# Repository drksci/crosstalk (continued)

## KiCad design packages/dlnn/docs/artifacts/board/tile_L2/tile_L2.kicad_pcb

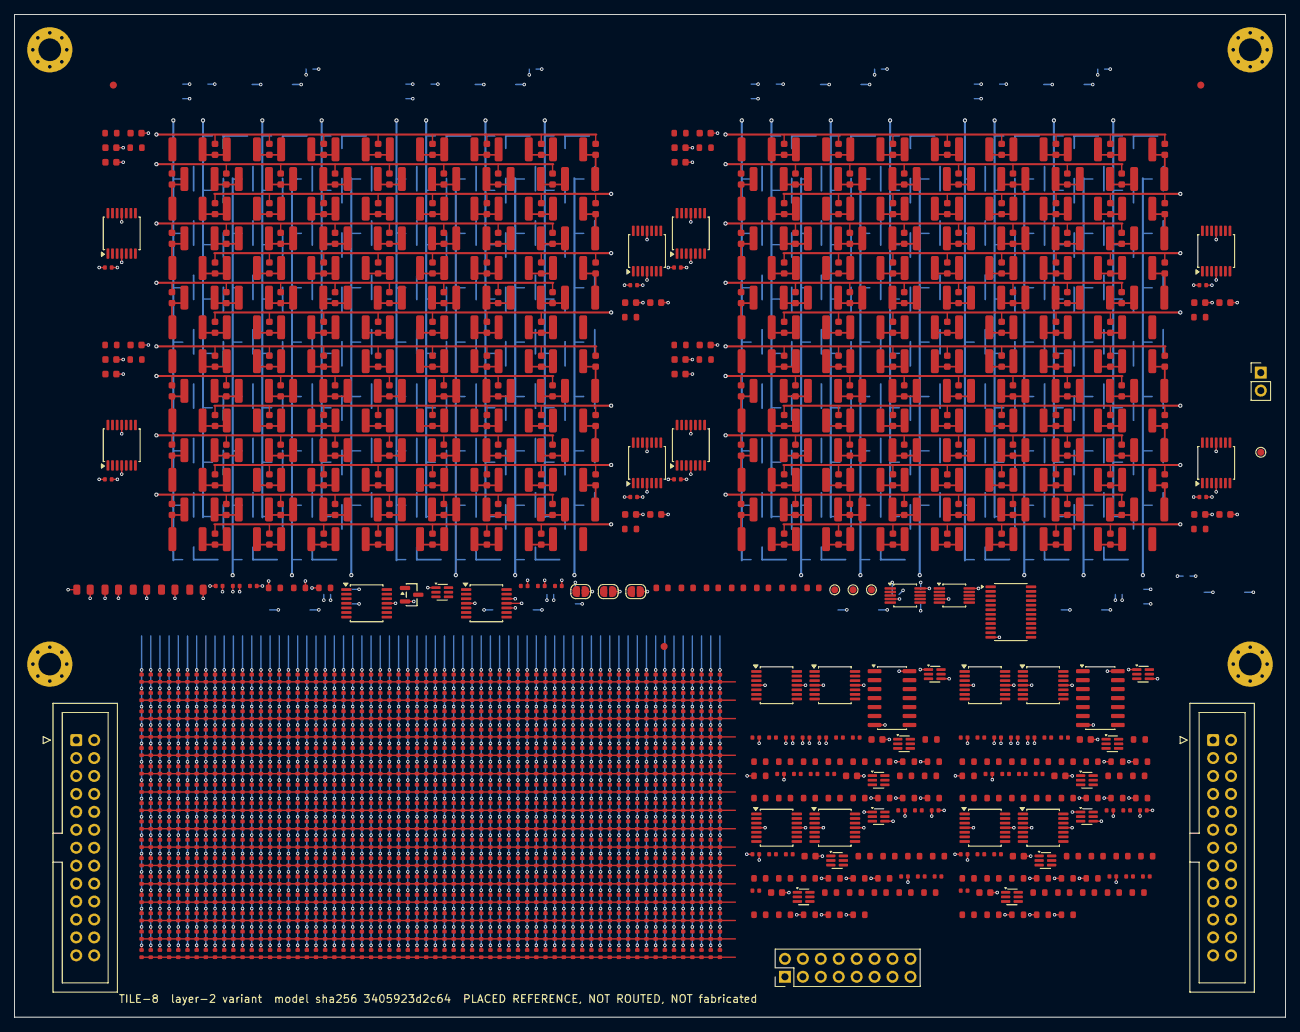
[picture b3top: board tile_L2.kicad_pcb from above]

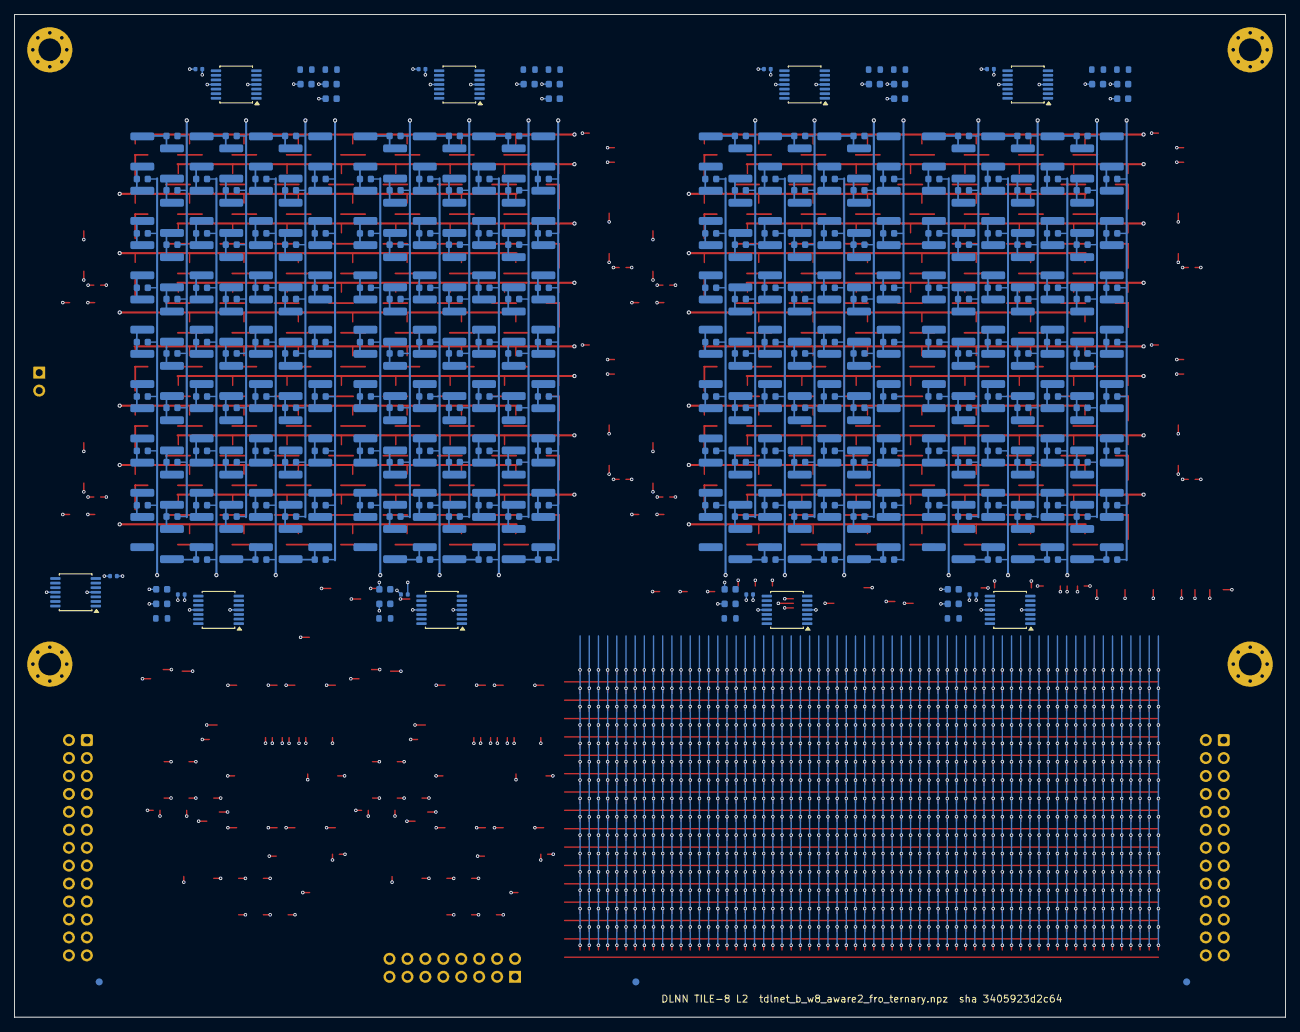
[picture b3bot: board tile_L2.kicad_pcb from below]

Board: 4 copper layers, 180.0 x 142.0 mm, 2211 parts (497 on the bottom side), 668 nets.

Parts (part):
C0_0_1, C0_0_2, C0_56_1, C0_56_2, C1_0_1, C1_0_2, C1_56_1, C1_56_2, C2_0_1, C2_0_2, C2_56_1, C2_56_2, C3_0_1, C3_0_2, C3_56_1, C3_56_2, C4_0_1, C4_0_2, C4_56_1, C4_56_2, C5_0_1, C5_0_2, C5_56_1, C5_56_2, C6_0_1, C6_0_2, C6_56_1, C6_56_2, C7_0_1, C7_0_2, C7_56_1, C7_56_2: 30p; C_0603_1608Metric
C0_1, C0_2, C0_3, C0_4, C0_5, C0_6, C0_7, C0_8, C0_9, C0_10, C0_11, C0_12, C0_13, C0_14, C0_15, C0_16, C0_17, C0_18, C0_19, C0_20, C0_21, C0_22, C0_23, C0_24, C0_25, C0_26, C0_27, C0_28, C0_29, C0_30, C0_31, C0_32, C0_33, C0_34, C0_35, C0_36, C0_37, C0_38, C0_39, C0_40, C0_41, C0_42, C0_43, C0_44, C0_45, C0_46, C0_47, C0_48, C0_49, C0_50, C0_51, C0_52, C0_53, C0_54, C0_55, C1_1, C1_2, C1_3, C1_4, C1_5, C1_6, C1_7, C1_8, C1_9, C1_10, C1_11, C1_12, C1_13, C1_14, C1_15, C1_16, C1_17, C1_18, C1_19, C1_20, C1_21, C1_22, C1_23, C1_24, C1_25, C1_26, C1_27, C1_28, C1_29, C1_30, C1_31, C1_32, C1_33, C1_34, C1_35, C1_36, C1_37, C1_38, C1_39, C1_40, C1_41, C1_42, C1_43, C1_44, C1_45, C1_46, C1_47, C1_48, C1_49, C1_50, C1_51, C1_52, C1_53, C1_54, C1_55, C2_1, C2_2, C2_3, C2_4, C2_5, C2_6, C2_7, C2_8, C2_9, C2_10, C2_11, C2_12, C2_13, C2_14, C2_15, C2_16, C2_17, C2_18, C2_19, C2_20, C2_21, C2_22, C2_23, C2_24, C2_25, C2_26, C2_27, C2_28, C2_29, C2_30, C2_31, C2_32, C2_33, C2_34, C2_35, C2_36, C2_37, C2_38, C2_39, C2_40, C2_41, C2_42, C2_43, C2_44, C2_45, C2_46, C2_47, C2_48, C2_49, C2_50, C2_51, C2_52, C2_53, C2_54, C2_55, C3_1, C3_2, C3_3, C3_4, C3_5, C3_6, C3_7, C3_8, C3_9, C3_10, C3_11, C3_12, C3_13, C3_14, C3_15, C3_16, C3_17, C3_18, C3_19, C3_20, C3_21, C3_22, C3_23, C3_24, C3_25, C3_26, C3_27, C3_28, C3_29, C3_30, C3_31, C3_32, C3_33, C3_34, C3_35, C3_36, C3_37, C3_38, C3_39, C3_40, C3_41, C3_42, C3_43, C3_44, C3_45, C3_46, C3_47, C3_48, C3_49, C3_50, C3_51, C3_52, C3_53, C3_54, C3_55, C4_1, C4_2, C4_3, C4_4, C4_5, C4_6, C4_7, C4_8, C4_9, C4_10, C4_11, C4_12, C4_13, C4_14, C4_15, C4_16, C4_17, C4_18, C4_19, C4_20, C4_21, C4_22, C4_23, C4_24, C4_25, C4_26, C4_27, C4_28, C4_29, C4_30, C4_31, C4_32, C4_33, C4_34, C4_35, C4_36, C4_37, C4_38, C4_39, C4_40, C4_41, C4_42, C4_43, C4_44, C4_45, C4_46, C4_47, C4_48, C4_49, C4_50, C4_51, C4_52, C4_53, C4_54, C4_55, C5_1, C5_2, C5_3, C5_4, C5_5, C5_6, C5_7, C5_8, C5_9, C5_10, C5_11, C5_12, C5_13, C5_14, C5_15, C5_16, C5_17, C5_18, C5_19, C5_20, C5_21, C5_22, C5_23, C5_24, C5_25, C5_26, C5_27, C5_28, C5_29, C5_30, C5_31, C5_32, C5_33, C5_34, C5_35, C5_36, C5_37, C5_38, C5_39, C5_40, C5_41, C5_42, C5_43, C5_44, C5_45, C5_46, C5_47, C5_48, C5_49, C5_50, C5_51, C5_52, C5_53, C5_54, C5_55, C6_1, C6_2, C6_3, C6_4, C6_5, C6_6, C6_7, C6_8, C6_9, C6_10, C6_11, C6_12, C6_13, C6_14, C6_15, C6_16, C6_17, C6_18, C6_19, C6_20, C6_21, C6_22, C6_23, C6_24, C6_25, C6_26, C6_27, C6_28, C6_29, C6_30, C6_31, C6_32, C6_33, C6_34, C6_35, C6_36, C6_37, C6_38, C6_39, C6_40, C6_41, C6_42, C6_43, C6_44, C6_45, C6_46, C6_47, C6_48, C6_49, C6_50, C6_51, C6_52, C6_53, C6_54, C6_55, C7_1, C7_2, C7_3, C7_4, C7_5, C7_6, C7_7, C7_8, C7_9, C7_10, C7_11, C7_12, C7_13, C7_14, C7_15, C7_16, C7_17, C7_18, C7_19, C7_20, C7_21, C7_22, C7_23, C7_24, C7_25, C7_26, C7_27, C7_28, C7_29, C7_30, C7_31, C7_32, C7_33, C7_34, C7_35, C7_36, C7_37, C7_38, C7_39, C7_40, C7_41, C7_42, C7_43, C7_44, C7_45, C7_46, C7_47, C7_48, C7_49, C7_50, C7_51, C7_52, C7_53, C7_54, C7_55: 120p; C_0603_1608Metric
CB1, CB2, CB3, CB4, CB5: 10u; C_0805_2012Metric
CBF0, CBF1, CBF2, CBF3, CBF4, CBF5, CBF6, CBF7: 100n; C_0402_1005Metric
CDA0, CDA1, CDA2, CDA3, CDA4, CDA5, CDA6, CDA7: 8.2p; C_0402_1005Metric
CDCS0, CDCS1, CDCS2, CDCS3: 100n; C_0402_1005Metric
CDDA0, CDDA1, CDDA2, CDDA3: 100n; C_0402_1005Metric
CDDAC0, CDDAC1: 100n; C_0402_1005Metric
CDIB0, CDIB1: 100n; C_0402_1005Metric
CDMUX1: 100n; C_0402_1005Metric
CDSH0, CDSH1: 100n; C_0402_1005Metric
CDTA0, CDTA1, CDTA2, CDTA3, CDTA4, CDTA5, CDTA6, CDTA7: 100n; C_0402_1005Metric
CDTB0, CDTB1, CDTB2, CDTB3, CDTB4, CDTB5, CDTB6, CDTB7: 100n; C_0402_1005Metric
CDVR1: 100n; C_0402_1005Metric
CFN0, CFN1, CFN2, CFN3, CFN4, CFN5, CFN6, CFN7: 15p; C_0402_1005Metric
CFP0, CFP1, CFP2, CFP3, CFP4, CFP5, CFP6, CFP7: 15p; C_0402_1005Metric
CH0, CH1, CH2, CH3, CH4, CH5, CH6, CH7: 560p; C_0603_1608Metric
CP0, CP1, CP2, CP3, CP4, CP5, CP6, CP7: 330p; C_0603_1608Metric
CREF1: 100n; C_0402_1005Metric
FID1, FID2, FID3, FID4, FID5, FID6: Fiducial_1mm_Mask2mm
H1, H2, H3, H4: MountingHole_3.2mm_M3_Pad_Via
JIN1: 2x13 IDC; IDC-Header_2x13_P2.54mm_Vertical
JMON1: MON; PinHeader_1x02_P2.54mm_Vertical
JOUT1: 2x13 IDC; IDC-Header_2x13_P2.54mm_Vertical
JPID0, JPID1, JPID2: ID; SolderJumper-2_P1.3mm_Open_RoundedPad1.0x1.5mm
JPS1: J_PS 2x8; PinHeader_2x08_P2.54mm_Vertical
L0_1, L0_2, L0_3, L0_4, L0_5, L0_6, L0_7, L0_8, L0_9, L0_10, L0_11, L0_12, L0_13, L0_14, L0_15, L0_16, L0_17, L0_18, L0_19, L0_20, L0_21, L0_22, L0_23, L0_24, L0_25, L0_26, L0_27, L0_28, L0_29, L0_30, L0_31, L0_32, L0_33, L0_34, L0_35, L0_36, L0_37, L0_38, L0_39, L0_40, L0_41, L0_42, L0_43, L0_44, L0_45, L0_46, L0_47, L0_48, L0_49, L0_50, L0_51, L0_52, L0_53, L0_54, L0_55, L0_56, L1_1, L1_2, L1_3, L1_4, L1_5, L1_6, L1_7, L1_8, L1_9, L1_10, L1_11, L1_12, L1_13, L1_14, L1_15, L1_16, L1_17, L1_18, L1_19, L1_20, L1_21, L1_22, L1_23, L1_24, L1_25, L1_26, L1_27, L1_28, L1_29, L1_30, L1_31, L1_32, L1_33, L1_34, L1_35, L1_36, L1_37, L1_38, L1_39, L1_40, L1_41, L1_42, L1_43, L1_44, L1_45, L1_46, L1_47, L1_48, L1_49, L1_50, L1_51, L1_52, L1_53, L1_54, L1_55, L1_56, L2_1, L2_2, L2_3, L2_4, L2_5, L2_6, L2_7, L2_8, L2_9, L2_10, L2_11, L2_12, L2_13, L2_14, L2_15, L2_16, L2_17, L2_18, L2_19, L2_20, L2_21, L2_22, L2_23, L2_24, L2_25, L2_26, L2_27, L2_28, L2_29, L2_30, L2_31, L2_32, L2_33, L2_34, L2_35, L2_36, L2_37, L2_38, L2_39, L2_40, L2_41, L2_42, L2_43, L2_44, L2_45, L2_46, L2_47, L2_48, L2_49, L2_50, L2_51, L2_52, L2_53, L2_54, L2_55, L2_56, L3_1, L3_2, L3_3, L3_4, L3_5, L3_6, L3_7, L3_8, L3_9, L3_10, L3_11, L3_12, L3_13, L3_14, L3_15, L3_16, L3_17, L3_18, L3_19, L3_20, L3_21, L3_22, L3_23, L3_24, L3_25, L3_26, L3_27, L3_28, L3_29, L3_30, L3_31, L3_32, L3_33, L3_34, L3_35, L3_36, L3_37, L3_38, L3_39, L3_40, L3_41, L3_42, L3_43, L3_44, L3_45, L3_46, L3_47, L3_48, L3_49, L3_50, L3_51, L3_52, L3_53, L3_54, L3_55, L3_56, L4_1, L4_2, L4_3, L4_4, L4_5, L4_6, L4_7, L4_8, L4_9, L4_10, L4_11, L4_12, L4_13, L4_14, L4_15, L4_16, L4_17, L4_18, L4_19, L4_20, L4_21, L4_22, L4_23, L4_24, L4_25, L4_26, L4_27, L4_28, L4_29, L4_30, L4_31, L4_32, L4_33, L4_34, L4_35, L4_36, L4_37, L4_38, L4_39, L4_40, L4_41, L4_42, L4_43, L4_44, L4_45, L4_46, L4_47, L4_48, L4_49, L4_50, L4_51, L4_52, L4_53, L4_54, L4_55, L4_56, L5_1, L5_2, L5_3, L5_4, L5_5, L5_6, L5_7, L5_8, L5_9, L5_10, L5_11, L5_12, L5_13, L5_14, L5_15, L5_16, L5_17, L5_18, L5_19, L5_20, L5_21, L5_22, L5_23, L5_24, L5_25, L5_26, L5_27, L5_28, L5_29, L5_30, L5_31, L5_32, L5_33, L5_34, L5_35, L5_36, L5_37, L5_38, L5_39, L5_40, L5_41, L5_42, L5_43, L5_44, L5_45, L5_46, L5_47, L5_48, L5_49, L5_50, L5_51, L5_52, L5_53, L5_54, L5_55, L5_56, L6_1, L6_2, L6_3, L6_4, L6_5, L6_6, L6_7, L6_8, L6_9, L6_10, L6_11, L6_12, L6_13, L6_14, L6_15, L6_16, L6_17, L6_18, L6_19, L6_20, L6_21, L6_22, L6_23, L6_24, L6_25, L6_26, L6_27, L6_28, L6_29, L6_30, L6_31, L6_32, L6_33, L6_34, L6_35, L6_36, L6_37, L6_38, L6_39, L6_40, L6_41, L6_42, L6_43, L6_44, L6_45, L6_46, L6_47, L6_48, L6_49, L6_50, L6_51, L6_52, L6_53, L6_54, L6_55, L6_56, L7_1, L7_2, L7_3, L7_4, L7_5, L7_6, L7_7, L7_8, L7_9, L7_10, L7_11, L7_12, L7_13, L7_14, L7_15, L7_16, L7_17, L7_18, L7_19, L7_20, L7_21, L7_22, L7_23, L7_24, L7_25, L7_26, L7_27, L7_28, L7_29, L7_30, L7_31, L7_32, L7_33, L7_34, L7_35, L7_36, L7_37, L7_38, L7_39, L7_40, L7_41, L7_42, L7_43, L7_44, L7_45, L7_46, L7_47, L7_48, L7_49, L7_50, L7_51, L7_52, L7_53, L7_54, L7_55, L7_56: 120u; L_1812_4532Metric
QD0, QD1, QD2, QD3, QD4, QD5, QD6, QD7: BCM847BS; SOT-363_SC-70-6
RB0, RB1, RB2, RB3, RB4, RB5, RB6, RB7: 9.09k; R_0603_1608Metric
RDA1_0, RDA1_1, RDA1_2, RDA1_3, RDA1_4, RDA1_5, RDA1_6, RDA1_7, RDA3_0, RDA3_1, RDA3_2, RDA3_3, RDA3_4, RDA3_5, RDA3_6, RDA3_7: 20k; R_0603_1608Metric
RDA2_0, RDA2_1, RDA2_2, RDA2_3, RDA2_4, RDA2_5, RDA2_6, RDA2_7, RDA4_0, RDA4_1, RDA4_2, RDA4_3, RDA4_4, RDA4_5, RDA4_6, RDA4_7: 10.5k; R_0603_1608Metric
RFN0, RFN1, RFN2, RFN3, RFN4, RFN5, RFN6, RFN7: 1.05k; R_0603_1608Metric
RFP0, RFP1, RFP2, RFP3, RFP4, RFP5, RFP6, RFP7: 1.05k; R_0603_1608Metric
RID0, RID1, RID2: 10k; R_0603_1608Metric
RLD1_0, RLD1_1, RLD1_2, RLD1_3, RLD1_4, RLD1_5, RLD1_6, RLD1_7, RLD2_0, RLD2_1, RLD2_2, RLD2_3, RLD2_4, RLD2_5, RLD2_6, RLD2_7: 1k; R_0603_1608Metric
RMIR1: 4.32k; R_0603_1608Metric
RO0, RO1, RO2, RO3, RO4, RO5, RO6, RO7: 15.4k; R_0603_1608Metric
RP0, RP1, RP2, RP3, RP4, RP5, RP6, RP7: 1k; R_0603_1608Metric
RPD1: 10k; R_0603_1608Metric
RPU1, RPU2, RPU3, RPU4: 10k; R_0603_1608Metric
RREF1: 2.49k; R_0603_1608Metric
RS0, RS1, RS2, RS3, RS4, RS5, RS6, RS7: 1k; R_0603_1608Metric
RT0, RT1, RT2, RT3, RT4, RT5, RT6, RT7: 1k; R_0603_1608Metric
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
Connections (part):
+3V3: CB3.1, CDDAC0.1, CDDAC1.1, CDMUX1.1, JIN1.21, JOUT1.21, RID0.1, RID1.1, RID2.1, RPU1.1, RPU2.1, RPU3.1, RPU4.1, UDAC0.1, UDAC1.1, UMUX1.3, UMUX1.24
+5VA: CB1.1, CB2.1, CDCS0.1, CDCS1.1, CDCS2.1, CDCS3.1, CDDA0.1, CDDA1.1, CDDA2.1, CDDA3.1, CDIB0.1, CDIB1.1, CDSH0.1, CDSH1.1, CDTA0.1, CDTA1.1, CDTA2.1, CDTA3.1, CDTA4.1, CDTA5.1, CDTA6.1, CDTA7.1, CDTB0.1, CDTB1.1, CDTB2.1, CDTB3.1, CDTB4.1, CDTB5.1, CDTB6.1, CDTB7.1, CDVR1.1, JIN1.17, JIN1.19, JOUT1.17, JOUT1.19, RLD1_0.1, RLD1_1.1, RLD1_2.1, RLD1_3.1, RLD1_4.1, RLD1_5.1, RLD1_6.1, RLD1_7.1, RLD2_0.1, RLD2_1.1, RLD2_2.1, RLD2_3.1, RLD2_4.1, RLD2_5.1, RLD2_6.1, RLD2_7.1, RMIR1.1, RO0.1, RO1.1, RO2.1, RO3.1, RO4.1, RO5.1, RO6.1, RO7.1, RREF1.1, UCS0.4, UCS1.4, UCS2.4, UCS3.4, UDA0.4, UDA1.4, UDA2.4, UDA3.4, UIB0.4, UIB1.4, USH0.14, USH1.14, UTA0.4, UTA1.4, UTA2.4, UTA3.4, UTA4.4, UTA5.4, UTA6.4, UTA7.4, UTB0.4, UTB1.4, UTB2.4, UTB3.4, UTB4.4, UTB5.4, UTB6.4, UTB7.4, UVR1.4
/ch0/DAIN: CDA0.1, RDA3_0.2, RDA4_0.1, UDA0.2
/ch0/DAIP: RDA1_0.2, RDA2_0.1, UDA0.3
/ch0/DAO: CDA0.2, RDA4_0.2, UDA0.1, USH0.1
/ch0/DC1: QD0.6, RDA1_0.1, RLD1_0.2
/ch0/DC2: QD0.3, RDA3_0.1, RLD2_0.2
/ch0/HOLD: CH0.1, UDA0.5, USH0.2
/ch0/ON: CFN0.2, QD0.2, RFN0.2, UCS0.7
/ch0/OP: CFP0.2, QD0.5, RFP0.2, UCS0.1
/ch0/TAIL: QD0.1, QD0.4, UT0.6
/ch1/DAIN: CDA1.1, RDA3_1.2, RDA4_1.1, UDA0.9
/ch1/DAIP: RDA1_1.2, RDA2_1.1, UDA0.10
/ch1/DAO: CDA1.2, RDA4_1.2, UDA0.8, USH0.4
/ch1/DC1: QD1.6, RDA1_1.1, RLD1_1.2
/ch1/DC2: QD1.3, RDA3_1.1, RLD2_1.2
/ch1/HOLD: CH1.1, UDA0.12, USH0.3
/ch1/ON: CFN1.2, QD1.2, RFN1.2, UCS0.14
/ch1/OP: CFP1.2, QD1.5, RFP1.2, UCS0.8
/ch1/TAIL: QD1.1, QD1.4, UT0.3
/ch2/DAIN: CDA2.1, RDA3_2.2, RDA4_2.1, UDA1.2
/ch2/DAIP: RDA1_2.2, RDA2_2.1, UDA1.3
/ch2/DAO: CDA2.2, RDA4_2.2, UDA1.1, USH0.8
/ch2/DC1: QD2.6, RDA1_2.1, RLD1_2.2
/ch2/DC2: QD2.3, RDA3_2.1, RLD2_2.2
/ch2/HOLD: CH2.1, UDA1.5, USH0.9
/ch2/ON: CFN2.2, QD2.2, RFN2.2, UCS1.7
/ch2/OP: CFP2.2, QD2.5, RFP2.2, UCS1.1
/ch2/TAIL: QD2.1, QD2.4, UT1.6
/ch3/DAIN: CDA3.1, RDA3_3.2, RDA4_3.1, UDA1.9
/ch3/DAIP: RDA1_3.2, RDA2_3.1, UDA1.10
/ch3/DAO: CDA3.2, RDA4_3.2, UDA1.8, USH0.11
/ch3/DC1: QD3.6, RDA1_3.1, RLD1_3.2
/ch3/DC2: QD3.3, RDA3_3.1, RLD2_3.2
/ch3/HOLD: CH3.1, UDA1.12, USH0.10
/ch3/ON: CFN3.2, QD3.2, RFN3.2, UCS1.14
/ch3/OP: CFP3.2, QD3.5, RFP3.2, UCS1.8
/ch3/TAIL: QD3.1, QD3.4, UT1.3
/ch4/DAIN: CDA4.1, RDA3_4.2, RDA4_4.1, UDA2.2
/ch4/DAIP: RDA1_4.2, RDA2_4.1, UDA2.3
/ch4/DAO: CDA4.2, RDA4_4.2, UDA2.1, USH1.1
/ch4/DC1: QD4.6, RDA1_4.1, RLD1_4.2
/ch4/DC2: QD4.3, RDA3_4.1, RLD2_4.2
/ch4/HOLD: CH4.1, UDA2.5, USH1.2
/ch4/ON: CFN4.2, QD4.2, RFN4.2, UCS2.7
/ch4/OP: CFP4.2, QD4.5, RFP4.2, UCS2.1
/ch4/TAIL: QD4.1, QD4.4, UT2.6
/ch5/DAIN: CDA5.1, RDA3_5.2, RDA4_5.1, UDA2.9
/ch5/DAIP: RDA1_5.2, RDA2_5.1, UDA2.10
/ch5/DAO: CDA5.2, RDA4_5.2, UDA2.8, USH1.4
/ch5/DC1: QD5.6, RDA1_5.1, RLD1_5.2
/ch5/DC2: QD5.3, RDA3_5.1, RLD2_5.2
/ch5/HOLD: CH5.1, UDA2.12, USH1.3
/ch5/ON: CFN5.2, QD5.2, RFN5.2, UCS2.14
/ch5/OP: CFP5.2, QD5.5, RFP5.2, UCS2.8
/ch5/TAIL: QD5.1, QD5.4, UT2.3
/ch6/DAIN: CDA6.1, RDA3_6.2, RDA4_6.1, UDA3.2
/ch6/DAIP: RDA1_6.2, RDA2_6.1, UDA3.3
/ch6/DAO: CDA6.2, RDA4_6.2, UDA3.1, USH1.8
/ch6/DC1: QD6.6, RDA1_6.1, RLD1_6.2
/ch6/DC2: QD6.3, RDA3_6.1, RLD2_6.2
/ch6/HOLD: CH6.1, UDA3.5, USH1.9
/ch6/ON: CFN6.2, QD6.2, RFN6.2, UCS3.7
/ch6/OP: CFP6.2, QD6.5, RFP6.2, UCS3.1
/ch6/TAIL: QD6.1, QD6.4, UT3.6
/ch7/DAIN: CDA7.1, RDA3_7.2, RDA4_7.1, UDA3.9
/ch7/DAIP: RDA1_7.2, RDA2_7.1, UDA3.10
/ch7/DAO: CDA7.2, RDA4_7.2, UDA3.8, USH1.11
/ch7/DC1: QD7.6, RDA1_7.1, RLD1_7.2
/ch7/DC2: QD7.3, RDA3_7.1, RLD2_7.2
/ch7/HOLD: CH7.1, UDA3.12, USH1.10
/ch7/ON: CFN7.2, QD7.2, RFN7.2, UCS3.14
/ch7/OP: CFP7.2, QD7.5, RFP7.2, UCS3.8
/ch7/TAIL: QD7.1, QD7.4, UT3.3
/connectors/SCL0: RPU2.2, UDAC0.2, UMUX1.5
/connectors/SCL1: RPU4.2, UDAC1.2, UMUX1.7
/connectors/SDA0: RPU1.2, UDAC0.3, UMUX1.4
/connectors/SDA1: RPU3.2, UDAC1.3, UMUX1.6
/connectors/TID0: JPID0.1, RID0.2, TPID0.1, UMUX1.1
/connectors/TID1: JPID1.1, RID1.2, TPID1.1, UMUX1.2
/connectors/TID2: JPID2.1, RID2.2, TPID2.1, UMUX1.21
/line0/IB: RS0.1, UIB0.1, UIB0.2
/line0/N0: C0_0_1.1, C0_0_2.1, L0_1.1, RS0.2, UTA0.3
/line0/N8: C0_8.1, L0_8.2, L0_9.1, UTB0.3
/line0/N16: C0_16.1, L0_16.2, L0_17.1, UTA0.5
/line0/N24: C0_24.1, L0_24.2, L0_25.1, UTB0.5
/line0/N28: C0_28.1, L0_28.2, L0_29.1
/line0/N32: C0_32.1, L0_32.2, L0_33.1, UTA0.10
/line0/N40: C0_40.1, L0_40.2, L0_41.1, UTB0.10
/line0/N48: C0_48.1, L0_48.2, L0_49.1, UTA0.12
/line0/N56: C0_56_1.1, C0_56_2.1, L0_56.2, RT0.1, UTB0.12
/line0/RC: CP0.1, RP0.2, UIB0.3
/line1/IB: RS1.1, UIB0.6, UIB0.7
/line1/N0: C1_0_1.1, C1_0_2.1, L1_1.1, RS1.2, UTA1.3
/line1/N8: C1_8.1, L1_8.2, L1_9.1, UTB1.3
/line1/N16: C1_16.1, L1_16.2, L1_17.1, UTA1.5
/line1/N24: C1_24.1, L1_24.2, L1_25.1, UTB1.5
/line1/N28: C1_28.1, L1_28.2, L1_29.1
/line1/N32: C1_32.1, L1_32.2, L1_33.1, UTA1.10
/line1/N40: C1_40.1, L1_40.2, L1_41.1, UTB1.10
/line1/N48: C1_48.1, L1_48.2, L1_49.1, UTA1.12
/line1/N56: C1_56_1.1, C1_56_2.1, L1_56.2, RT1.1, UTB1.12
/line1/RC: CP1.1, RP1.2, UIB0.5
/line2/IB: RS2.1, UIB0.8, UIB0.9
/line2/N0: C2_0_1.1, C2_0_2.1, L2_1.1, RS2.2, UTA2.3
/line2/N8: C2_8.1, L2_8.2, L2_9.1, UTB2.3
/line2/N16: C2_16.1, L2_16.2, L2_17.1, UTA2.5
/line2/N24: C2_24.1, L2_24.2, L2_25.1, UTB2.5
/line2/N28: C2_28.1, L2_28.2, L2_29.1
/line2/N32: C2_32.1, L2_32.2, L2_33.1, UTA2.10
/line2/N40: C2_40.1, L2_40.2, L2_41.1, UTB2.10
/line2/N48: C2_48.1, L2_48.2, L2_49.1, UTA2.12
/line2/N56: C2_56_1.1, C2_56_2.1, L2_56.2, RT2.1, UTB2.12
/line2/RC: CP2.1, RP2.2, UIB0.10
/line3/IB: RS3.1, UIB0.13, UIB0.14
/line3/N0: C3_0_1.1, C3_0_2.1, L3_1.1, RS3.2, UTA3.3
/line3/N8: C3_8.1, L3_8.2, L3_9.1, UTB3.3
/line3/N16: C3_16.1, L3_16.2, L3_17.1, UTA3.5
/line3/N24: C3_24.1, L3_24.2, L3_25.1, UTB3.5
/line3/N28: C3_28.1, L3_28.2, L3_29.1
/line3/N32: C3_32.1, L3_32.2, L3_33.1, UTA3.10
/line3/N40: C3_40.1, L3_40.2, L3_41.1, UTB3.10
/line3/N48: C3_48.1, L3_48.2, L3_49.1, UTA3.12
/line3/N56: C3_56_1.1, C3_56_2.1, L3_56.2, RT3.1, UTB3.12
/line3/RC: CP3.1, RP3.2, UIB0.12
/line4/IB: RS4.1, UIB1.1, UIB1.2
/line4/N0: C4_0_1.1, C4_0_2.1, L4_1.1, RS4.2, UTA4.3
/line4/N8: C4_8.1, L4_8.2, L4_9.1, UTB4.3
/line4/N16: C4_16.1, L4_16.2, L4_17.1, UTA4.5
/line4/N24: C4_24.1, L4_24.2, L4_25.1, UTB4.5
/line4/N28: C4_28.1, L4_28.2, L4_29.1
/line4/N32: C4_32.1, L4_32.2, L4_33.1, UTA4.10
/line4/N40: C4_40.1, L4_40.2, L4_41.1, UTB4.10
/line4/N48: C4_48.1, L4_48.2, L4_49.1, UTA4.12
/line4/N56: C4_56_1.1, C4_56_2.1, L4_56.2, RT4.1, UTB4.12
/line4/RC: CP4.1, RP4.2, UIB1.3
/line5/IB: RS5.1, UIB1.6, UIB1.7
/line5/N0: C5_0_1.1, C5_0_2.1, L5_1.1, RS5.2, UTA5.3
/line5/N8: C5_8.1, L5_8.2, L5_9.1, UTB5.3
/line5/N16: C5_16.1, L5_16.2, L5_17.1, UTA5.5
/line5/N24: C5_24.1, L5_24.2, L5_25.1, UTB5.5
/line5/N28: C5_28.1, L5_28.2, L5_29.1
/line5/N32: C5_32.1, L5_32.2, L5_33.1, UTA5.10
/line5/N40: C5_40.1, L5_40.2, L5_41.1, UTB5.10
/line5/N48: C5_48.1, L5_48.2, L5_49.1, UTA5.12
/line5/N56: C5_56_1.1, C5_56_2.1, L5_56.2, RT5.1, UTB5.12
/line5/RC: CP5.1, RP5.2, UIB1.5
/line6/IB: RS6.1, UIB1.8, UIB1.9
/line6/N0: C6_0_1.1, C6_0_2.1, L6_1.1, RS6.2, UTA6.3
/line6/N8: C6_8.1, L6_8.2, L6_9.1, UTB6.3
/line6/N16: C6_16.1, L6_16.2, L6_17.1, UTA6.5
/line6/N24: C6_24.1, L6_24.2, L6_25.1, UTB6.5
/line6/N28: C6_28.1, L6_28.2, L6_29.1
/line6/N32: C6_32.1, L6_32.2, L6_33.1, UTA6.10
/line6/N40: C6_40.1, L6_40.2, L6_41.1, UTB6.10
/line6/N48: C6_48.1, L6_48.2, L6_49.1, UTA6.12
/line6/N56: C6_56_1.1, C6_56_2.1, L6_56.2, RT6.1, UTB6.12
/line6/RC: CP6.1, RP6.2, UIB1.10
/line7/IB: RS7.1, UIB1.13, UIB1.14
/line7/N0: C7_0_1.1, C7_0_2.1, L7_1.1, RS7.2, UTA7.3
/line7/N8: C7_8.1, L7_8.2, L7_9.1, UTB7.3
/line7/N16: C7_16.1, L7_16.2, L7_17.1, UTA7.5
/line7/N24: C7_24.1, L7_24.2, L7_25.1, UTB7.5
/line7/N28: C7_28.1, L7_28.2, L7_29.1
/line7/N32: C7_32.1, L7_32.2, L7_33.1, UTA7.10
/line7/N40: C7_40.1, L7_40.2, L7_41.1, UTB7.10
/line7/N48: C7_48.1, L7_48.2, L7_49.1, UTA7.12
/line7/N56: C7_56_1.1, C7_56_2.1, L7_56.2, RT7.1, UTB7.12
/line7/RC: CP7.1, RP7.2, UIB1.12
/power/PK_UVR1_3: UVR1.8, UVR1.9
/power/PK_UVR1_4: UVR1.13, UVR1.14
/power/V2R5: CREF1.1, RREF1.2, UREF1.1, UVR1.3, UVR1.5
BIAS0: CBF0.1, RB0.1, UDAC0.6
BIAS1: CBF1.1, RB1.1, UDAC0.7
BIAS2: CBF2.1, RB2.1, UDAC0.8
BIAS3: CBF3.1, RB3.1, UDAC0.9
BIAS4: CBF4.1, RB4.1, UDAC1.6
BIAS5: CBF5.1, RB5.1, UDAC1.7
BIAS6: CBF6.1, RB6.1, UDAC1.8
BIAS7: CBF7.1, RB7.1, UDAC1.9
GND: C0_0_1.2, C0_0_2.2, C0_1.2, C0_2.2, C0_3.2, C0_4.2, C0_5.2, C0_6.2, C0_7.2, C0_8.2, C0_9.2, C0_10.2, C0_11.2, C0_12.2, C0_13.2, C0_14.2, C0_15.2, C0_16.2, C0_17.2, C0_18.2, C0_19.2, C0_20.2, C0_21.2, C0_22.2, C0_23.2, C0_24.2, C0_25.2, C0_26.2, C0_27.2, C0_28.2, C0_29.2, C0_30.2, C0_31.2, C0_32.2, C0_33.2, C0_34.2, C0_35.2, C0_36.2, C0_37.2, C0_38.2, C0_39.2, C0_40.2, C0_41.2, C0_42.2, C0_43.2, C0_44.2, C0_45.2, C0_46.2, C0_47.2, C0_48.2, C0_49.2, C0_50.2, C0_51.2, C0_52.2, C0_53.2, C0_54.2, C0_55.2, C0_56_1.2, C0_56_2.2, C1_0_1.2, C1_0_2.2, C1_1.2, C1_2.2, C1_3.2, C1_4.2, C1_5.2, C1_6.2, C1_7.2, C1_8.2, C1_9.2, C1_10.2, C1_11.2, C1_12.2, C1_13.2, C1_14.2, C1_15.2, C1_16.2, C1_17.2, C1_18.2, C1_19.2, C1_20.2, C1_21.2, C1_22.2, C1_23.2, C1_24.2, C1_25.2, C1_26.2, C1_27.2, C1_28.2, C1_29.2, C1_30.2, C1_31.2, C1_32.2, C1_33.2, C1_34.2, C1_35.2, C1_36.2, C1_37.2, C1_38.2, C1_39.2, C1_40.2, C1_41.2, C1_42.2, C1_43.2, C1_44.2, C1_45.2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
MIRB: RMIR1.2, UT0.2, UT0.5, UT1.2, UT1.5, UT2.2, UT2.5, UT3.2, UT3.5, UTR1.2, UTR1.6
unnamed: C0_1.1, L0_1.2, L0_2.1
unnamed: C0_2.1, L0_2.2, L0_3.1
unnamed: C0_3.1, L0_3.2, L0_4.1
unnamed: C0_4.1, L0_4.2, L0_5.1
unnamed: C0_5.1, L0_5.2, L0_6.1
unnamed: C0_6.1, L0_6.2, L0_7.1
unnamed: C0_7.1, L0_7.2, L0_8.1
unnamed: C0_9.1, L0_9.2, L0_10.1
unnamed: C0_10.1, L0_10.2, L0_11.1
unnamed: C0_11.1, L0_11.2, L0_12.1
unnamed: C0_12.1, L0_12.2, L0_13.1
unnamed: C0_13.1, L0_13.2, L0_14.1
unnamed: C0_14.1, L0_14.2, L0_15.1
unnamed: C0_15.1, L0_15.2, L0_16.1
unnamed: C0_17.1, L0_17.2, L0_18.1
unnamed: C0_18.1, L0_18.2, L0_19.1
unnamed: C0_19.1, L0_19.2, L0_20.1
unnamed: C0_20.1, L0_20.2, L0_21.1
unnamed: C0_21.1, L0_21.2, L0_22.1
unnamed: C0_22.1, L0_22.2, L0_23.1
unnamed: C0_23.1, L0_23.2, L0_24.1
unnamed: C0_25.1, L0_25.2, L0_26.1
unnamed: C0_26.1, L0_26.2, L0_27.1
unnamed: C0_27.1, L0_27.2, L0_28.1
unnamed: C0_29.1, L0_29.2, L0_30.1
unnamed: C0_30.1, L0_30.2, L0_31.1
unnamed: C0_31.1, L0_31.2, L0_32.1
unnamed: C0_33.1, L0_33.2, L0_34.1
unnamed: C0_34.1, L0_34.2, L0_35.1
unnamed: C0_35.1, L0_35.2, L0_36.1
unnamed: C0_36.1, L0_36.2, L0_37.1
unnamed: C0_37.1, L0_37.2, L0_38.1
unnamed: C0_38.1, L0_38.2, L0_39.1
unnamed: C0_39.1, L0_39.2, L0_40.1
unnamed: C0_41.1, L0_41.2, L0_42.1
unnamed: C0_42.1, L0_42.2, L0_43.1
unnamed: C0_43.1, L0_43.2, L0_44.1
unnamed: C0_44.1, L0_44.2, L0_45.1
unnamed: C0_45.1, L0_45.2, L0_46.1
unnamed: C0_46.1, L0_46.2, L0_47.1
unnamed: C0_47.1, L0_47.2, L0_48.1
unnamed: C0_49.1, L0_49.2, L0_50.1
unnamed: C0_50.1, L0_50.2, L0_51.1
unnamed: C0_51.1, L0_51.2, L0_52.1
unnamed: C0_52.1, L0_52.2, L0_53.1
unnamed: C0_53.1, L0_53.2, L0_54.1
unnamed: C0_54.1, L0_54.2, L0_55.1
unnamed: C0_55.1, L0_55.2, L0_56.1
unnamed: C1_1.1, L1_1.2, L1_2.1
unnamed: C1_2.1, L1_2.2, L1_3.1
unnamed: C1_3.1, L1_3.2, L1_4.1
unnamed: C1_4.1, L1_4.2, L1_5.1
unnamed: C1_5.1, L1_5.2, L1_6.1
unnamed: C1_6.1, L1_6.2, L1_7.1
unnamed: C1_7.1, L1_7.2, L1_8.1
unnamed: C1_9.1, L1_9.2, L1_10.1
unnamed: C1_10.1, L1_10.2, L1_11.1
unnamed: C1_11.1, L1_11.2, L1_12.1
unnamed: C1_12.1, L1_12.2, L1_13.1
unnamed: C1_13.1, L1_13.2, L1_14.1
unnamed: C1_14.1, L1_14.2, L1_15.1
unnamed: C1_15.1, L1_15.2, L1_16.1
unnamed: C1_17.1, L1_17.2, L1_18.1
unnamed: C1_18.1, L1_18.2, L1_19.1
unnamed: C1_19.1, L1_19.2, L1_20.1
unnamed: C1_20.1, L1_20.2, L1_21.1
unnamed: C1_21.1, L1_21.2, L1_22.1
unnamed: C1_22.1, L1_22.2, L1_23.1
unnamed: C1_23.1, L1_23.2, L1_24.1
unnamed: C1_25.1, L1_25.2, L1_26.1
unnamed: C1_26.1, L1_26.2, L1_27.1
unnamed: C1_27.1, L1_27.2, L1_28.1
unnamed: C1_29.1, L1_29.2, L1_30.1
unnamed: C1_30.1, L1_30.2, L1_31.1
unnamed: C1_31.1, L1_31.2, L1_32.1
unnamed: C1_33.1, L1_33.2, L1_34.1
unnamed: C1_34.1, L1_34.2, L1_35.1
unnamed: C1_35.1, L1_35.2, L1_36.1
unnamed: C1_36.1, L1_36.2, L1_37.1
unnamed: C1_37.1, L1_37.2, L1_38.1
unnamed: C1_38.1, L1_38.2, L1_39.1
unnamed: C1_39.1, L1_39.2, L1_40.1
unnamed: C1_41.1, L1_41.2, L1_42.1
unnamed: C1_42.1, L1_42.2, L1_43.1
unnamed: C1_43.1, L1_43.2, L1_44.1
unnamed: C1_44.1, L1_44.2, L1_45.1
unnamed: C1_45.1, L1_45.2, L1_46.1
unnamed: C1_46.1, L1_46.2, L1_47.1
unnamed: C1_47.1, L1_47.2, L1_48.1
unnamed: C1_49.1, L1_49.2, L1_50.1
unnamed: C1_50.1, L1_50.2, L1_51.1
unnamed: C1_51.1, L1_51.2, L1_52.1
unnamed: C1_52.1, L1_52.2, L1_53.1
unnamed: C1_53.1, L1_53.2, L1_54.1
unnamed: C1_54.1, L1_54.2, L1_55.1
unnamed: C1_55.1, L1_55.2, L1_56.1
unnamed: C2_1.1, L2_1.2, L2_2.1
unnamed: C2_2.1, L2_2.2, L2_3.1
unnamed: C2_3.1, L2_3.2, L2_4.1
unnamed: C2_4.1, L2_4.2, L2_5.1
unnamed: C2_5.1, L2_5.2, L2_6.1
unnamed: C2_6.1, L2_6.2, L2_7.1
unnamed: C2_7.1, L2_7.2, L2_8.1
unnamed: C2_9.1, L2_9.2, L2_10.1
unnamed: C2_10.1, L2_10.2, L2_11.1
unnamed: C2_11.1, L2_11.2, L2_12.1
unnamed: C2_12.1, L2_12.2, L2_13.1
unnamed: C2_13.1, L2_13.2, L2_14.1
unnamed: C2_14.1, L2_14.2, L2_15.1
unnamed: C2_15.1, L2_15.2, L2_16.1
unnamed: C2_17.1, L2_17.2, L2_18.1
unnamed: C2_18.1, L2_18.2, L2_19.1
unnamed: C2_19.1, L2_19.2, L2_20.1
unnamed: C2_20.1, L2_20.2, L2_21.1
unnamed: C2_21.1, L2_21.2, L2_22.1
unnamed: C2_22.1, L2_22.2, L2_23.1
unnamed: C2_23.1, L2_23.2, L2_24.1
unnamed: C2_25.1, L2_25.2, L2_26.1
unnamed: C2_26.1, L2_26.2, L2_27.1
unnamed: C2_27.1, L2_27.2, L2_28.1
unnamed: C2_29.1, L2_29.2, L2_30.1
unnamed: C2_30.1, L2_30.2, L2_31.1
unnamed: C2_31.1, L2_31.2, L2_32.1
unnamed: C2_33.1, L2_33.2, L2_34.1
unnamed: C2_34.1, L2_34.2, L2_35.1
unnamed: C2_35.1, L2_35.2, L2_36.1
unnamed: C2_36.1, L2_36.2, L2_37.1
unnamed: C2_37.1, L2_37.2, L2_38.1
unnamed: C2_38.1, L2_38.2, L2_39.1
unnamed: C2_39.1, L2_39.2, L2_40.1
unnamed: C2_41.1, L2_41.2, L2_42.1
unnamed: C2_42.1, L2_42.2, L2_43.1
unnamed: C2_43.1, L2_43.2, L2_44.1
unnamed: C2_44.1, L2_44.2, L2_45.1
unnamed: C2_45.1, L2_45.2, L2_46.1
unnamed: C2_46.1, L2_46.2, L2_47.1
unnamed: C2_47.1, L2_47.2, L2_48.1
unnamed: C2_49.1, L2_49.2, L2_50.1
unnamed: C2_50.1, L2_50.2, L2_51.1
unnamed: C2_51.1, L2_51.2, L2_52.1
unnamed: C2_52.1, L2_52.2, L2_53.1
unnamed: C2_53.1, L2_53.2, L2_54.1
unnamed: C2_54.1, L2_54.2, L2_55.1
unnamed: C2_55.1, L2_55.2, L2_56.1
unnamed: C3_1.1, L3_1.2, L3_2.1
unnamed: C3_2.1, L3_2.2, L3_3.1
unnamed: C3_3.1, L3_3.2, L3_4.1
unnamed: C3_4.1, L3_4.2, L3_5.1
unnamed: C3_5.1, L3_5.2, L3_6.1
unnamed: C3_6.1, L3_6.2, L3_7.1
unnamed: C3_7.1, L3_7.2, L3_8.1
unnamed: C3_9.1, L3_9.2, L3_10.1
unnamed: C3_10.1, L3_10.2, L3_11.1
unnamed: C3_11.1, L3_11.2, L3_12.1
unnamed: C3_12.1, L3_12.2, L3_13.1
unnamed: C3_13.1, L3_13.2, L3_14.1
unnamed: C3_14.1, L3_14.2, L3_15.1
unnamed: C3_15.1, L3_15.2, L3_16.1
unnamed: C3_17.1, L3_17.2, L3_18.1
unnamed: C3_18.1, L3_18.2, L3_19.1
unnamed: C3_19.1, L3_19.2, L3_20.1
unnamed: C3_20.1, L3_20.2, L3_21.1
unnamed: C3_21.1, L3_21.2, L3_22.1
unnamed: C3_22.1, L3_22.2, L3_23.1
unnamed: C3_23.1, L3_23.2, L3_24.1
unnamed: C3_25.1, L3_25.2, L3_26.1
unnamed: C3_26.1, L3_26.2, L3_27.1
unnamed: C3_27.1, L3_27.2, L3_28.1
unnamed: C3_29.1, L3_29.2, L3_30.1
unnamed: C3_30.1, L3_30.2, L3_31.1
unnamed: C3_31.1, L3_31.2, L3_32.1
unnamed: C3_33.1, L3_33.2, L3_34.1
unnamed: C3_34.1, L3_34.2, L3_35.1
unnamed: C3_35.1, L3_35.2, L3_36.1
unnamed: C3_36.1, L3_36.2, L3_37.1
unnamed: C3_37.1, L3_37.2, L3_38.1
unnamed: C3_38.1, L3_38.2, L3_39.1
unnamed: C3_39.1, L3_39.2, L3_40.1
unnamed: C3_41.1, L3_41.2, L3_42.1
unnamed: C3_42.1, L3_42.2, L3_43.1
unnamed: C3_43.1, L3_43.2, L3_44.1
unnamed: C3_44.1, L3_44.2, L3_45.1
unnamed: C3_45.1, L3_45.2, L3_46.1
unnamed: C3_46.1, L3_46.2, L3_47.1
unnamed: C3_47.1, L3_47.2, L3_48.1
unnamed: C3_49.1, L3_49.2, L3_50.1
unnamed: C3_50.1, L3_50.2, L3_51.1
unnamed: C3_51.1, L3_51.2, L3_52.1
unnamed: C3_52.1, L3_52.2, L3_53.1
unnamed: C3_53.1, L3_53.2, L3_54.1
unnamed: C3_54.1, L3_54.2, L3_55.1
unnamed: C3_55.1, L3_55.2, L3_56.1
unnamed: C4_1.1, L4_1.2, L4_2.1
unnamed: C4_2.1, L4_2.2, L4_3.1
unnamed: C4_3.1, L4_3.2, L4_4.1
unnamed: C4_4.1, L4_4.2, L4_5.1
unnamed: C4_5.1, L4_5.2, L4_6.1
unnamed: C4_6.1, L4_6.2, L4_7.1
unnamed: C4_7.1, L4_7.2, L4_8.1
unnamed: C4_9.1, L4_9.2, L4_10.1
unnamed: C4_10.1, L4_10.2, L4_11.1
unnamed: C4_11.1, L4_11.2, L4_12.1
unnamed: C4_12.1, L4_12.2, L4_13.1
unnamed: C4_13.1, L4_13.2, L4_14.1
unnamed: C4_14.1, L4_14.2, L4_15.1
unnamed: C4_15.1, L4_15.2, L4_16.1
unnamed: C4_17.1, L4_17.2, L4_18.1
unnamed: C4_18.1, L4_18.2, L4_19.1
unnamed: C4_19.1, L4_19.2, L4_20.1
unnamed: C4_20.1, L4_20.2, L4_21.1
unnamed: C4_21.1, L4_21.2, L4_22.1
unnamed: C4_22.1, L4_22.2, L4_23.1
unnamed: C4_23.1, L4_23.2, L4_24.1
unnamed: C4_25.1, L4_25.2, L4_26.1
unnamed: C4_26.1, L4_26.2, L4_27.1
unnamed: C4_27.1, L4_27.2, L4_28.1
unnamed: C4_29.1, L4_29.2, L4_30.1
unnamed: C4_30.1, L4_30.2, L4_31.1
unnamed: C4_31.1, L4_31.2, L4_32.1
unnamed: C4_33.1, L4_33.2, L4_34.1
unnamed: C4_34.1, L4_34.2, L4_35.1
unnamed: C4_35.1, L4_35.2, L4_36.1
unnamed: C4_36.1, L4_36.2, L4_37.1
unnamed: C4_37.1, L4_37.2, L4_38.1
unnamed: C4_38.1, L4_38.2, L4_39.1
unnamed: C4_39.1, L4_39.2, L4_40.1
unnamed: C4_41.1, L4_41.2, L4_42.1
unnamed: C4_42.1, L4_42.2, L4_43.1
unnamed: C4_43.1, L4_43.2, L4_44.1
unnamed: C4_44.1, L4_44.2, L4_45.1
unnamed: C4_45.1, L4_45.2, L4_46.1
unnamed: C4_46.1, L4_46.2, L4_47.1
unnamed: C4_47.1, L4_47.2, L4_48.1
unnamed: C4_49.1, L4_49.2, L4_50.1
unnamed: C4_50.1, L4_50.2, L4_51.1
unnamed: C4_51.1, L4_51.2, L4_52.1
unnamed: C4_52.1, L4_52.2, L4_53.1
unnamed: C4_53.1, L4_53.2, L4_54.1
unnamed: C4_54.1, L4_54.2, L4_55.1
unnamed: C4_55.1, L4_55.2, L4_56.1
unnamed: C5_1.1, L5_1.2, L5_2.1
unnamed: C5_2.1, L5_2.2, L5_3.1
unnamed: C5_3.1, L5_3.2, L5_4.1
unnamed: C5_4.1, L5_4.2, L5_5.1
unnamed: C5_5.1, L5_5.2, L5_6.1
unnamed: C5_6.1, L5_6.2, L5_7.1
unnamed: C5_7.1, L5_7.2, L5_8.1
unnamed: C5_9.1, L5_9.2, L5_10.1
unnamed: C5_10.1, L5_10.2, L5_11.1
unnamed: C5_11.1, L5_11.2, L5_12.1
unnamed: C5_12.1, L5_12.2, L5_13.1
unnamed: C5_13.1, L5_13.2, L5_14.1
unnamed: C5_14.1, L5_14.2, L5_15.1
unnamed: C5_15.1, L5_15.2, L5_16.1
unnamed: C5_17.1, L5_17.2, L5_18.1
unnamed: C5_18.1, L5_18.2, L5_19.1
unnamed: C5_19.1, L5_19.2, L5_20.1
unnamed: C5_20.1, L5_20.2, L5_21.1
unnamed: C5_21.1, L5_21.2, L5_22.1
unnamed: C5_22.1, L5_22.2, L5_23.1
unnamed: C5_23.1, L5_23.2, L5_24.1
unnamed: C5_25.1, L5_25.2, L5_26.1
unnamed: C5_26.1, L5_26.2, L5_27.1
unnamed: C5_27.1, L5_27.2, L5_28.1
unnamed: C5_29.1, L5_29.2, L5_30.1
unnamed: C5_30.1, L5_30.2, L5_31.1
unnamed: C5_31.1, L5_31.2, L5_32.1
unnamed: C5_33.1, L5_33.2, L5_34.1
unnamed: C5_34.1, L5_34.2, L5_35.1
unnamed: C5_35.1, L5_35.2, L5_36.1
unnamed: C5_36.1, L5_36.2, L5_37.1
unnamed: C5_37.1, L5_37.2, L5_38.1
unnamed: C5_38.1, L5_38.2, L5_39.1
unnamed: C5_39.1, L5_39.2, L5_40.1
unnamed: C5_41.1, L5_41.2, L5_42.1
unnamed: C5_42.1, L5_42.2, L5_43.1
unnamed: C5_43.1, L5_43.2, L5_44.1
unnamed: C5_44.1, L5_44.2, L5_45.1
unnamed: C5_45.1, L5_45.2, L5_46.1
unnamed: C5_46.1, L5_46.2, L5_47.1
unnamed: C5_47.1, L5_47.2, L5_48.1
unnamed: C5_49.1, L5_49.2, L5_50.1
unnamed: C5_50.1, L5_50.2, L5_51.1
unnamed: C5_51.1, L5_51.2, L5_52.1
unnamed: C5_52.1, L5_52.2, L5_53.1
unnamed: C5_53.1, L5_53.2, L5_54.1
unnamed: C5_54.1, L5_54.2, L5_55.1
unnamed: C5_55.1, L5_55.2, L5_56.1
unnamed: C6_1.1, L6_1.2, L6_2.1
unnamed: C6_2.1, L6_2.2, L6_3.1
unnamed: C6_3.1, L6_3.2, L6_4.1
unnamed: C6_4.1, L6_4.2, L6_5.1
unnamed: C6_5.1, L6_5.2, L6_6.1
unnamed: C6_6.1, L6_6.2, L6_7.1
unnamed: C6_7.1, L6_7.2, L6_8.1
unnamed: C6_9.1, L6_9.2, L6_10.1
unnamed: C6_10.1, L6_10.2, L6_11.1
unnamed: C6_11.1, L6_11.2, L6_12.1
unnamed: C6_12.1, L6_12.2, L6_13.1
unnamed: C6_13.1, L6_13.2, L6_14.1
unnamed: C6_14.1, L6_14.2, L6_15.1
unnamed: C6_15.1, L6_15.2, L6_16.1
unnamed: C6_17.1, L6_17.2, L6_18.1
unnamed: C6_18.1, L6_18.2, L6_19.1
unnamed: C6_19.1, L6_19.2, L6_20.1
unnamed: C6_20.1, L6_20.2, L6_21.1
unnamed: C6_21.1, L6_21.2, L6_22.1
unnamed: C6_22.1, L6_22.2, L6_23.1
unnamed: C6_23.1, L6_23.2, L6_24.1
unnamed: C6_25.1, L6_25.2, L6_26.1
unnamed: C6_26.1, L6_26.2, L6_27.1
unnamed: C6_27.1, L6_27.2, L6_28.1
unnamed: C6_29.1, L6_29.2, L6_30.1
unnamed: C6_30.1, L6_30.2, L6_31.1
unnamed: C6_31.1, L6_31.2, L6_32.1
unnamed: C6_33.1, L6_33.2, L6_34.1
unnamed: C6_34.1, L6_34.2, L6_35.1
unnamed: C6_35.1, L6_35.2, L6_36.1
unnamed: C6_36.1, L6_36.2, L6_37.1
unnamed: C6_37.1, L6_37.2, L6_38.1
unnamed: C6_38.1, L6_38.2, L6_39.1
unnamed: C6_39.1, L6_39.2, L6_40.1
unnamed: C6_41.1, L6_41.2, L6_42.1
unnamed: C6_42.1, L6_42.2, L6_43.1
unnamed: C6_43.1, L6_43.2, L6_44.1
unnamed: C6_44.1, L6_44.2, L6_45.1
unnamed: C6_45.1, L6_45.2, L6_46.1
unnamed: C6_46.1, L6_46.2, L6_47.1
unnamed: C6_47.1, L6_47.2, L6_48.1
unnamed: C6_49.1, L6_49.2, L6_50.1
unnamed: C6_50.1, L6_50.2, L6_51.1
unnamed: C6_51.1, L6_51.2, L6_52.1
unnamed: C6_52.1, L6_52.2, L6_53.1
unnamed: C6_53.1, L6_53.2, L6_54.1
unnamed: C6_54.1, L6_54.2, L6_55.1
unnamed: C6_55.1, L6_55.2, L6_56.1
unnamed: C7_1.1, L7_1.2, L7_2.1
unnamed: C7_2.1, L7_2.2, L7_3.1
unnamed: C7_3.1, L7_3.2, L7_4.1
unnamed: C7_4.1, L7_4.2, L7_5.1
unnamed: C7_5.1, L7_5.2, L7_6.1
unnamed: C7_6.1, L7_6.2, L7_7.1
unnamed: C7_7.1, L7_7.2, L7_8.1
unnamed: C7_9.1, L7_9.2, L7_10.1
unnamed: C7_10.1, L7_10.2, L7_11.1
unnamed: C7_11.1, L7_11.2, L7_12.1
unnamed: C7_12.1, L7_12.2, L7_13.1
unnamed: C7_13.1, L7_13.2, L7_14.1
unnamed: C7_14.1, L7_14.2, L7_15.1
unnamed: C7_15.1, L7_15.2, L7_16.1
unnamed: C7_17.1, L7_17.2, L7_18.1
unnamed: C7_18.1, L7_18.2, L7_19.1
unnamed: C7_19.1, L7_19.2, L7_20.1
unnamed: C7_20.1, L7_20.2, L7_21.1
unnamed: C7_21.1, L7_21.2, L7_22.1
unnamed: C7_22.1, L7_22.2, L7_23.1
unnamed: C7_23.1, L7_23.2, L7_24.1
unnamed: C7_25.1, L7_25.2, L7_26.1
unnamed: C7_26.1, L7_26.2, L7_27.1
unnamed: C7_27.1, L7_27.2, L7_28.1
unnamed: C7_29.1, L7_29.2, L7_30.1
unnamed: C7_30.1, L7_30.2, L7_31.1
unnamed: C7_31.1, L7_31.2, L7_32.1
unnamed: C7_33.1, L7_33.2, L7_34.1
unnamed: C7_34.1, L7_34.2, L7_35.1
unnamed: C7_35.1, L7_35.2, L7_36.1
unnamed: C7_36.1, L7_36.2, L7_37.1
unnamed: C7_37.1, L7_37.2, L7_38.1
unnamed: C7_38.1, L7_38.2, L7_39.1
unnamed: C7_39.1, L7_39.2, L7_40.1
unnamed: C7_41.1, L7_41.2, L7_42.1
unnamed: C7_42.1, L7_42.2, L7_43.1
unnamed: C7_43.1, L7_43.2, L7_44.1
unnamed: C7_44.1, L7_44.2, L7_45.1
unnamed: C7_45.1, L7_45.2, L7_46.1
unnamed: C7_46.1, L7_46.2, L7_47.1
unnamed: C7_47.1, L7_47.2, L7_48.1
unnamed: C7_49.1, L7_49.2, L7_50.1
unnamed: C7_50.1, L7_50.2, L7_51.1
unnamed: C7_51.1, L7_51.2, L7_52.1
unnamed: C7_52.1, L7_52.2, L7_53.1
unnamed: C7_53.1, L7_53.2, L7_54.1
unnamed: C7_54.1, L7_54.2, L7_55.1
unnamed: C7_55.1, L7_55.2, L7_56.1
OUT0: JOUT1.1, UDA0.6, UDA0.7
OUT1: JOUT1.3, UDA0.13, UDA0.14
OUT2: JOUT1.5, UDA1.6, UDA1.7
OUT3: JOUT1.7, UDA1.13, UDA1.14
OUT4: JOUT1.9, UDA2.6, UDA2.7
OUT5: JOUT1.11, UDA2.13, UDA2.14
OUT6: JOUT1.13, UDA3.6, UDA3.7
OUT7: JOUT1.15, UDA3.13, UDA3.14
SCL: JIN1.23, JOUT1.23, UMUX1.22
SDA: JIN1.22, JOUT1.22, UMUX1.23
SH_CLK: JIN1.24, JOUT1.24, RPD1.1, USH0.5, USH0.6, USH0.12, USH0.13, USH1.5, USH1.6, USH1.12, USH1.13
SIG0: JIN1.1, RP0.1
SIG1: JIN1.3, RP1.1
SIG2: JIN1.5, RP2.1
SIG3: JIN1.7, RP3.1
SIG4: JIN1.9, RP4.1
SIG5: JIN1.11, RP5.1
SIG6: JIN1.13, RP6.1
SIG7: JIN1.15, RP7.1
SN0: CFN0.1, JPS1.2, RB0.2, RFN0.1, RO0.2, RXP_0_0_0.2, RXP_0_0_1.2, RXP_0_0_2.2, RXP_0_0_3.2, RXP_0_0_4.2, RXP_0_0_5.2, RXP_0_0_6.2, RXP_0_0_7.2, RXP_0_1_0.2, RXP_0_1_1.2, RXP_0_1_2.2, RXP_0_1_3.2, RXP_0_1_4.2, RXP_0_1_5.2, RXP_0_1_6.2, RXP_0_1_7.2, RXP_0_2_0.2, RXP_0_2_1.2, RXP_0_2_2.2, RXP_0_2_3.2, RXP_0_2_4.2, RXP_0_2_5.2, RXP_0_2_6.2, RXP_0_2_7.2, RXP_0_3_0.2, RXP_0_3_1.2, RXP_0_3_2.2, RXP_0_3_3.2, RXP_0_3_4.2, RXP_0_3_5.2, RXP_0_3_6.2, RXP_0_3_7.2, RXP_0_4_0.2, RXP_0_4_1.2, RXP_0_4_2.2, RXP_0_4_3.2, RXP_0_4_4.2, RXP_0_4_5.2, RXP_0_4_6.2, RXP_0_4_7.2, RXP_0_5_0.2, RXP_0_5_1.2, RXP_0_5_2.2, RXP_0_5_3.2, RXP_0_5_4.2, RXP_0_5_5.2, RXP_0_5_6.2, RXP_0_5_7.2, RXP_0_6_0.2, RXP_0_6_1.2, RXP_0_6_2.2, RXP_0_6_3.2, RXP_0_6_4.2, RXP_0_6_5.2, RXP_0_6_6.2, RXP_0_6_7.2, RXP_0_7_0.2, RXP_0_7_1.2, RXP_0_7_2.2, RXP_0_7_3.2, RXP_0_7_4.2, RXP_0_7_5.2, RXP_0_7_6.2, RXP_0_7_7.2, UCS0.6
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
